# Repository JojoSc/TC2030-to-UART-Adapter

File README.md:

# TC2030-to-UART-Adapter
Adapter to connect the TC2030 IDC cable to a USB-to-UART Adapter. This can be used to program ESP32 boards (or any other UART compatible microcontroller) without a big footprint on the PCB.

Boot and Enable/Reset buttons are included on this board, so they don't have to be on your PCB. This saves a lot of space, since only the tiny TC2030 footprint needs to be included on the final PCB.

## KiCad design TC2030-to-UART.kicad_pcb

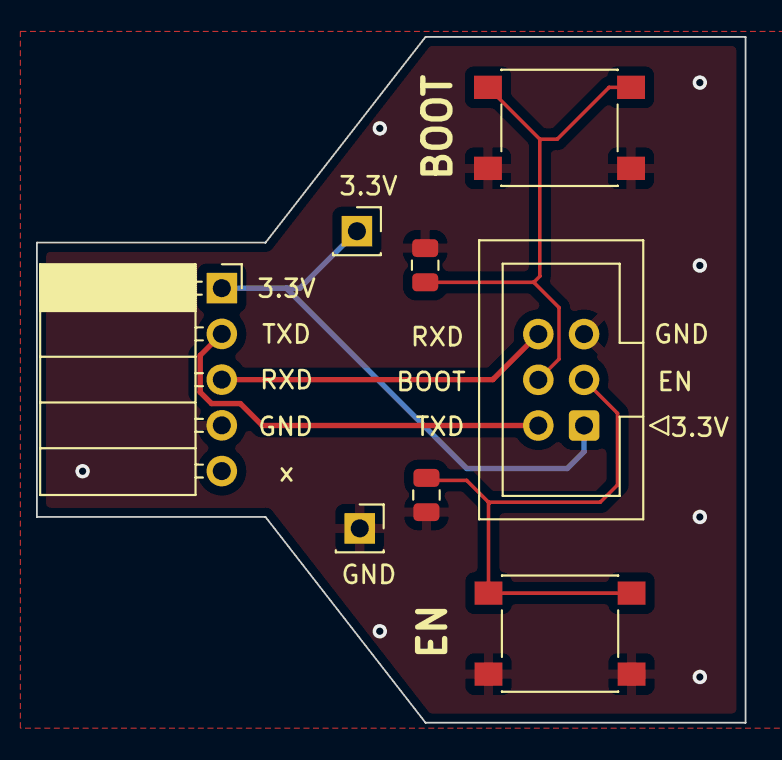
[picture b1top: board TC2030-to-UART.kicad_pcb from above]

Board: 2 copper layers, 39.4 x 38.1 mm, 8 parts (0 on the bottom side), 6 nets.

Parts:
3.3V: Conn_01x01_Female; PinSocket_1x01_P2.54mm_Vertical
BOOT: SW_Push_Dual; SW_Push_1P1T_NO_6x6mm_H9.5mm
C1, C2: 100nF; C_0805_2012Metric
EN: SW_Push_Dual; SW_Push_1P1T_NO_6x6mm_H9.5mm
GND: Conn_01x01_Female; PinSocket_1x01_P2.54mm_Vertical
J1: Conn_01x05_Female; PinSocket_1x05_P2.54mm_Horizontal
J2: Conn_02x03_Odd_Even; IDC-Header_2x03_P2.54mm_Vertical

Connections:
+3.3V: 3.3V.1, J1.1, J2.1
BOOT: BOOT.1, C2.1, J2.4
EN: C1.1, EN.1, J2.3
GND: BOOT.2, C1.2, C2.2, EN.2, GND.1, J1.4, J2.5
RXD: J1.3, J2.6
TXD: J1.2, J2.2

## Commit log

2022-09-18 Added Readme
